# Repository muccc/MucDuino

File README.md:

# MucDuino
Nice Form Factor Arduino Nano Boards
## MucDuino_Banana

## MucDuino_Cherry

## MucDuino_Strawberry

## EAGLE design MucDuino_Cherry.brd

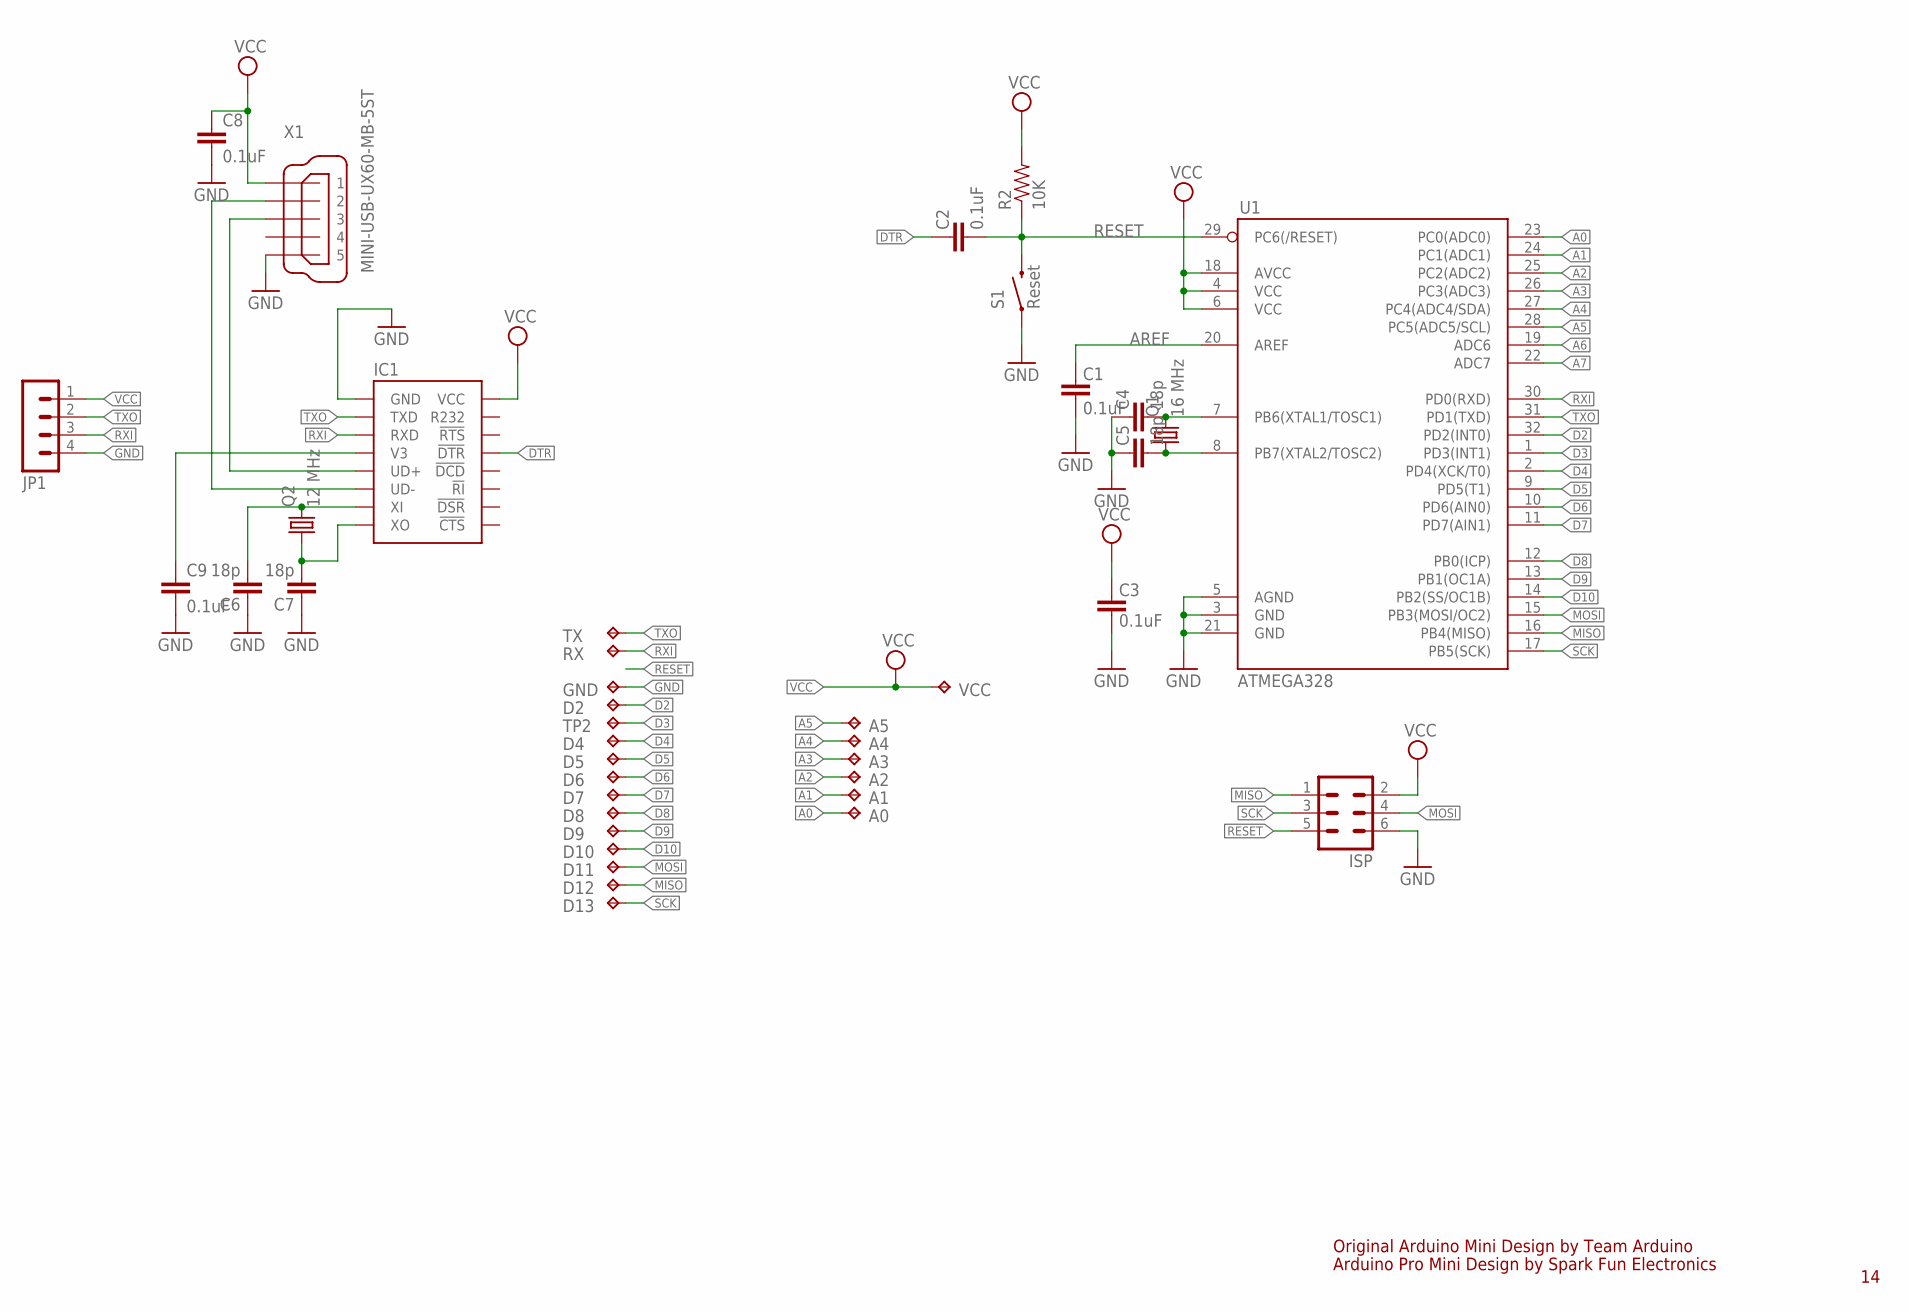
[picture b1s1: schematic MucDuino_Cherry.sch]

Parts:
A0, A1, A2, A3, A4, A5: TPPAD1-13; P1-13
C1, C2, C3, C8, C9: 0.1uF; 0603-CAP
C4, C5, C6, C7: 18p; 0603-CAP
D2, D4, D5, D6, D7, D8, D9, D10, D11, D12, D13: TPPAD1-13; P1-13
GND: TPPAD1-13; P1-13
IC1: CH340G; SOP16-209MM
ISP: MA03-2
JP1: MA04-1
Q1: 16 MHz; HC49UP
Q2: 12 MHz; HC49UP
R2: 10K; 0603-RES
RX: TPPAD1-13; P1-13
S1: Reset; TACTILE-SWITCH-SMD-ALT01
TP2: TPPAD1-13; P1-13
TX: TPPAD1-13; P1-13
U1: ATMEGA328; TQFP32-08
VCC: TPPAD1-13; P1-13
X1: MINI-USB-UX60-MB-5ST; UX60-MB-5ST

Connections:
A0: A0.TP, U1.23 (PC0(ADC0))
A1: A1.TP, U1.24 (PC1(ADC1))
A2: A2.TP, U1.25 (PC2(ADC2))
A3: A3.TP, U1.26 (PC3(ADC3))
A4: A4.TP, U1.27 (PC4(ADC4/SDA))
A5: A5.TP, U1.28 (PC5(ADC5/SCL))
A6: U1.19 (ADC6)
A7: U1.22 (ADC7)
AREF: C1.2, U1.20 (AREF)
D2: D2.TP, U1.32 (PD2(INT0))
D3: TP2.TP, U1.1 (PD3(INT1))
D4: D4.TP, U1.2 (PD4(XCK/T0))
D5: D5.TP, U1.9 (PD5(T1))
D6: D6.TP, U1.10 (PD6(AIN0))
D7: D7.TP, U1.11 (PD7(AIN1))
D8: D8.TP, U1.12 (PB0(ICP))
D9: D9.TP, U1.13 (PB1(OC1A))
D10: D10.TP, U1.14 (PB2(SS/OC1B))
DTR: C2.2, IC1.P$13 (!DTR)
GND: C1.1, C3.1, C4.2, C5.2, C6.2, C7.2, C8.2, C9.2, GND.TP, IC1.P$1 (GND), ISP.6, JP1.4, S1.1, S1.2 (1), U1.3 (GND), U1.5 (AGND), U1.21 (GND), X1.5
MISO: D12.TP, ISP.1, U1.16 (PB4(MISO))
MOSI: D11.TP, ISP.4, U1.15 (PB3(MOSI/OC2))
unnamed: C5.1, Q1.1, U1.8 (PB7(XTAL2/TOSC2))
unnamed: C4.1, Q1.2, U1.7 (PB6(XTAL1/TOSC1))
unnamed: C9.1, IC1.P$4 (V3)
unnamed: C6.1, IC1.P$7 (XI), Q2.2
unnamed: C7.1, IC1.P$8 (XO), Q2.1
unnamed: IC1.P$5 (UD+), X1.3
unnamed: IC1.P$6 (UD-), X1.2
RESET: C2.1, ISP.5, R2.1, S1.3 (2), S1.4 (2), U1.29 (PC6(/RESET))
RXI: IC1.P$3 (RXD), JP1.3, RX.TP, U1.30 (PD0(RXD))
SCK: D13.TP, ISP.3, U1.17 (PB5(SCK))
TXO: IC1.P$2 (TXD), JP1.2, TX.TP, U1.31 (PD1(TXD))
VCC: C3.2, C8.1, IC1.P$16 (VCC), ISP.2, JP1.1, R2.2, U1.4 (VCC), U1.6 (VCC), U1.18 (AVCC), VCC.TP, X1.1

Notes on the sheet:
Original Arduino Mini Design by Team Arduino
Arduino Pro Mini Design by Spark Fun Electronics

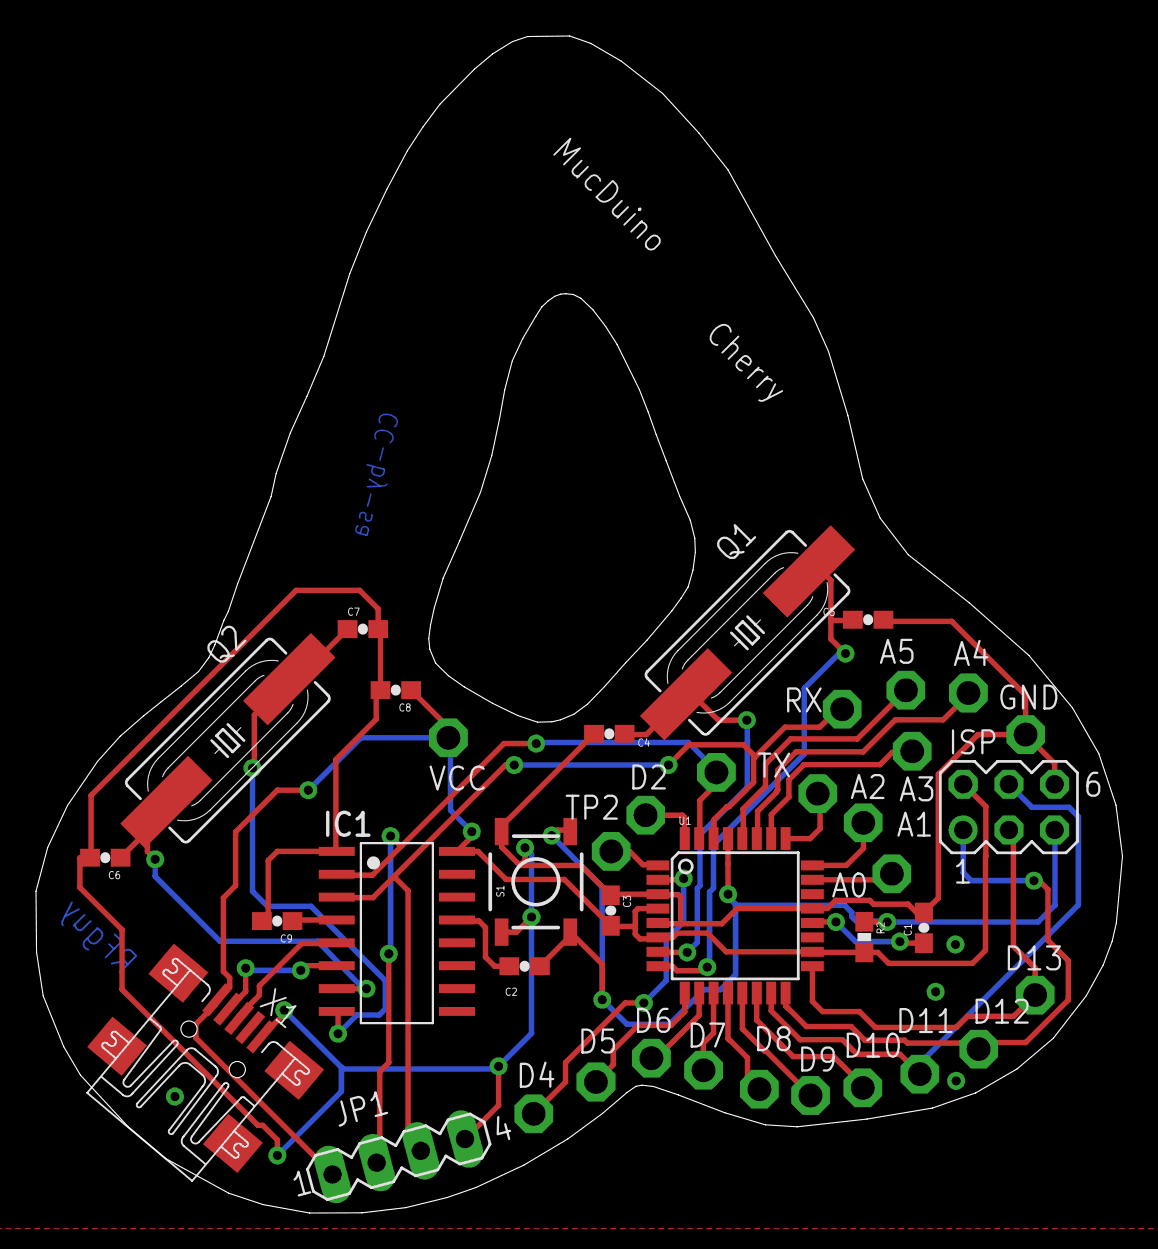
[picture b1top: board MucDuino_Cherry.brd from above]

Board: 2 copper layers, 60.4 x 65.4 mm, 40 parts (0 on the bottom side), 32 nets.

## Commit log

2015-07-18 Now here is the Banana Version of the Arduino Nano Board, like the WTFduino, but with Eagle Schematics, more will follow.
2015-07-18 Ad Cherry variant of MucDuino, fix Banana Version, ad USB Uart Datascheet
2015-07-18 Ad Strawberry Variant, have fun
2015-07-19 LICENSE, images and partlist
2015-07-19 LICENSE switch and markdown
2017-10-30 CC-by-sa license added on board
2017-10-30 CC License
    Added CC-by-sa marker on board
2017-10-30 CC License
    Added CC-by-sa marker to board
